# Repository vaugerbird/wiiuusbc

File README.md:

# wiiuusbc

A simple mod board for the WiiU gamepad that replaces the stock connector with a USB C port. The CC pins are connected and use 2 56kΩ resistors that allow for 500mA charging.

## Parts

Only 3 parts are used (other than the board).

* 1x of GCT USB4105-GF-A: [Mouser](https://www.mouser.com/ProductDetail/640-USB4105-GF-A) - [Digikey](https://www.digikey.com/en/products/detail/gct/USB4105-GF-A/11198441)
* 2x of ROHM SFR01MZPF5602: [Mouser]([https://www.mouser.com/ProductDetail/ROHM-Semiconductor/SFR01MZPF5602](https://www.mouser.com/ProductDetail/ROHM-Semiconductor/SFR01MZPF5602?qs=byeeYqUIh0PMHn%2FWHQ30Hw%3D%3D)) - [Digikey](https://www.digikey.com/en/products/detail/rohm-semiconductor/SFR01MZPF5602/16009123)

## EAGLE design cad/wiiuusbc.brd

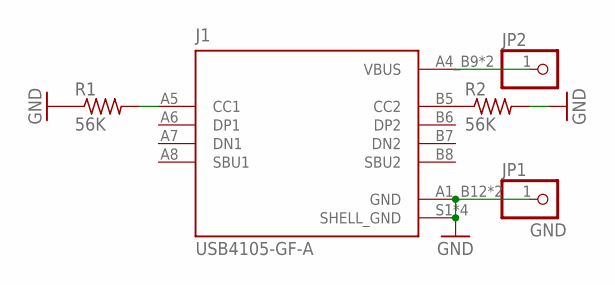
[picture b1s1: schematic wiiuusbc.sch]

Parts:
J1: USB4105-GF-A; GCT_USB4105-GF-A
JP1, JP2: PINHD-1X1; 1X01
R1, R2: 56K; R0402

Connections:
CC1: J1.A5 (CC1), R1.2
CC2: J1.B5 (CC2), R2.1
GND: J1.A1_B12 (GND), J1.B1_A12 (GND), J1.S1 (SHELL_GND), J1.S2 (SHELL_GND), J1.S3 (SHELL_GND), J1.S4 (SHELL_GND), JP1.1, R1.1, R2.2
VCC: J1.A4_B9 (VBUS), J1.B4_A9 (VBUS), JP2.1

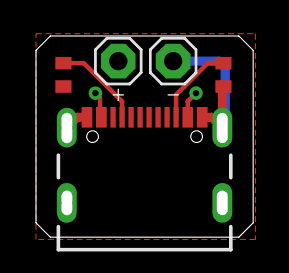
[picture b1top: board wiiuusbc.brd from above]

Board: 2 copper layers, 12.1 x 11.2 mm, 5 parts (0 on the bottom side), 4 nets.

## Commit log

2023-05-13 add board files
2023-05-13 connect CC lines and update readme
2023-05-13 Add images
2023-05-13 Fix the stupid readme
2023-05-24 Fix mouser resistor link
2023-05-24 Update silkscreen
